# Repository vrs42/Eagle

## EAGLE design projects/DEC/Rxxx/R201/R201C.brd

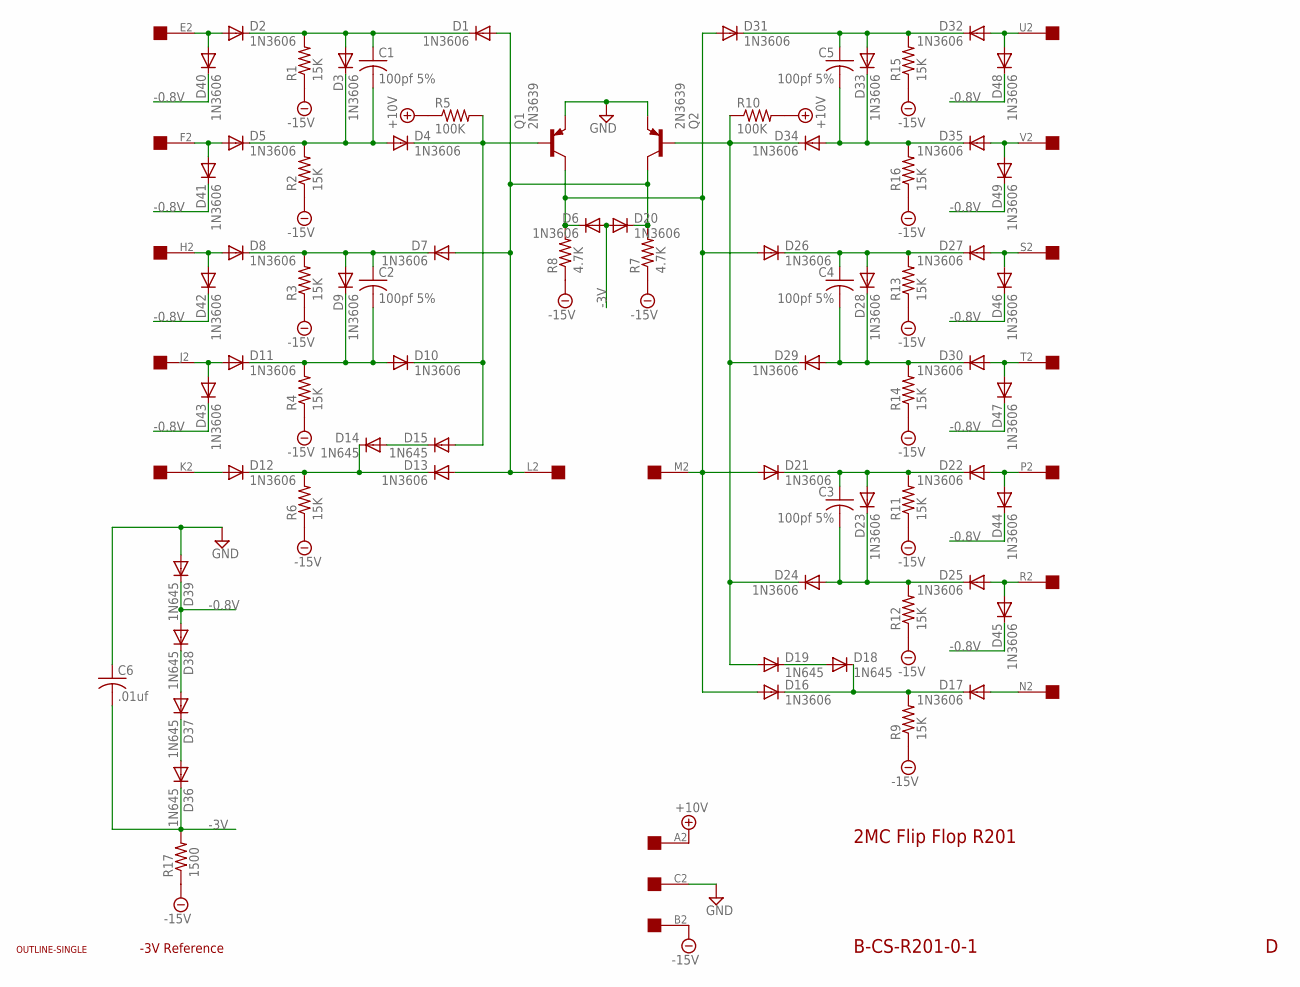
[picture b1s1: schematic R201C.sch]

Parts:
C1, C2, C3, C4, C5: 100pf 5%; C050-025X075
C6: .01uf; C050-025X075
D1, D2, D3, D4, D5, D6, D7, D8, D9, D10, D11, D12, D13, D16, D17, D20, D21, D22, D23, D24, D25, D26, D27, D28, D29, D30, D31, D32, D33, D34, D35, D40, D41, D42, D43, D44, D45, D46, D47, D48, D49: 1N3606; DO35-10
D14, D15, D18, D19, D36, D37, D38, D39: 1N645; DO35-10
Q1, Q2: 2N3639; TO39
R1, R2, R3, R4, R6, R9, R11, R12, R13, R14, R15, R16: 15K; 0207/10
R5, R10: 100K; 0207/10
R7, R8: 4.7K; 0207/10
R17: 1500; 0207/10
U$1: OUTLINE-SINGLE; SINGLE
U$2: EDGE-1; EDGE-CON1

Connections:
+10V: R5.1, R10.2, U$2.A2
-0.8V: D38.A, D39.C, D40.C, D41.C, D42.C, D43.C, D44.C, D45.C, D46.C, D47.C, D48.C, D49.C
-3V: C6.2, D6.A, D20.A, D36.C, R17.2
-15V: R1.1, R2.1, R3.1, R4.1, R6.1, R7.1, R8.1, R9.1, R11.1, R12.1, R13.1, R14.1, R15.1, R16.1, R17.1, U$2.B2
GND: C6.1, D39.A, Q1.1 (E), Q2.1 (E), U$2.C2
L: D1.A, D7.A, D13.A, D20.C, Q2.3 (C), R7.2, U$2.L2
M: D6.C, D16.A, D21.A, D26.A, D31.A, Q1.3 (C), R8.2, U$2.M2
unnamed: D5.A, D41.A, U$2.F2
unnamed: C5.1, D31.C, D32.C, D33.A, R15.2
unnamed: C1.2, D3.C, D4.A, D5.C, R2.2
unnamed: C1.1, D1.C, D2.C, D3.A, R1.2
unnamed: D12.A, U$2.K2
unnamed: D19.A, D24.C, D29.C, D34.C, Q2.2 (B), R10.1
unnamed: D32.A, D48.A, U$2.U2
unnamed: C5.2, D33.C, D34.A, D35.C, R16.2
unnamed: D17.A, U$2.N2
unnamed: D2.A, D40.A, U$2.E2
unnamed: D35.A, D49.A, U$2.V2
unnamed: D18.A, D19.C
unnamed: D37.A, D38.C
unnamed: D4.C, D10.C, D15.A, Q1.2 (B), R5.2
unnamed: D14.A, D15.C
unnamed: D36.A, D37.C
unnamed: D22.A, D44.A, U$2.P2
unnamed: D12.C, D13.C, D14.C, R6.2
unnamed: D8.A, D42.A, U$2.H2
unnamed: D16.C, D17.C, D18.C, R9.2
unnamed: D11.A, D43.A, U$2.J2
unnamed: C2.2, D9.C, D10.A, D11.C, R4.2
unnamed: D27.A, D46.A, U$2.S2
unnamed: C2.1, D7.C, D8.C, D9.A, R3.2
unnamed: D30.A, D47.A, U$2.T2
unnamed: C4.2, D28.C, D29.A, D30.C, R14.2
unnamed: C4.1, D26.C, D27.C, D28.A, R13.2
unnamed: D25.A, D45.A, U$2.R2
unnamed: C3.2, D23.C, D24.A, D25.C, R12.2
unnamed: C3.1, D21.C, D22.C, D23.A, R11.2

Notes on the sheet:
2MC Flip Flop R201
B-CS-R201-0-1
-3V Reference

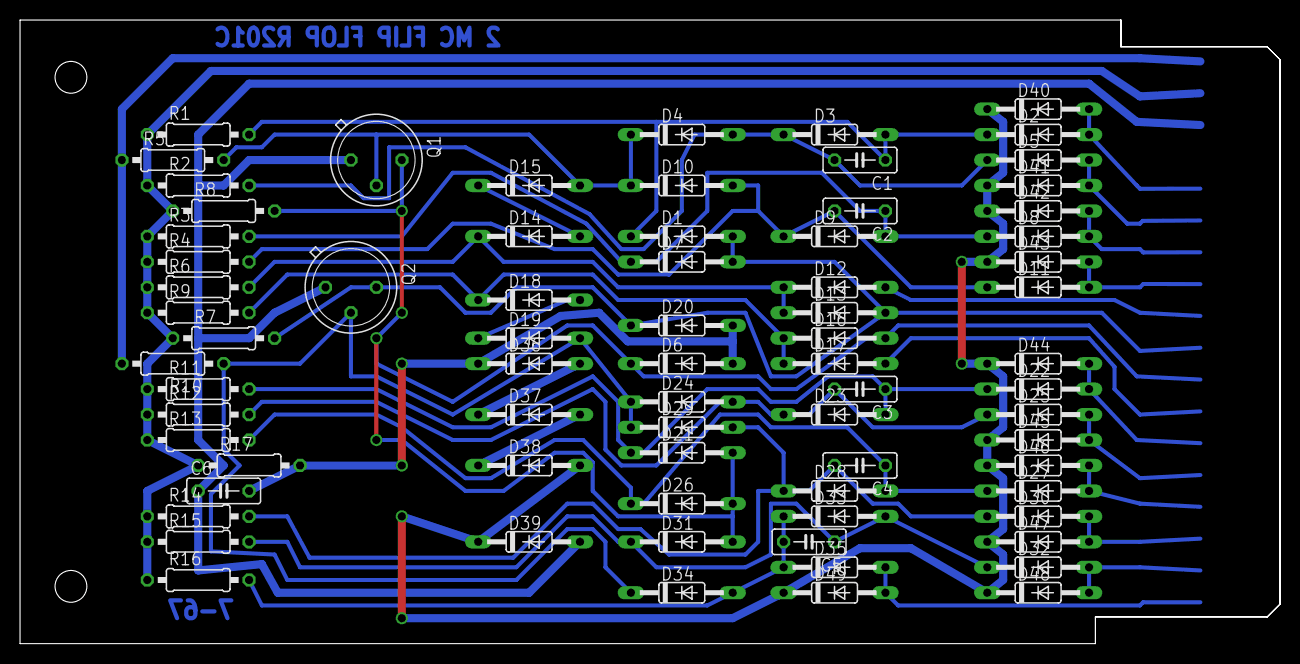
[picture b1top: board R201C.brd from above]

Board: 2 copper layers, 125.7 x 62.2 mm, 76 parts (0 on the bottom side), 37 nets.

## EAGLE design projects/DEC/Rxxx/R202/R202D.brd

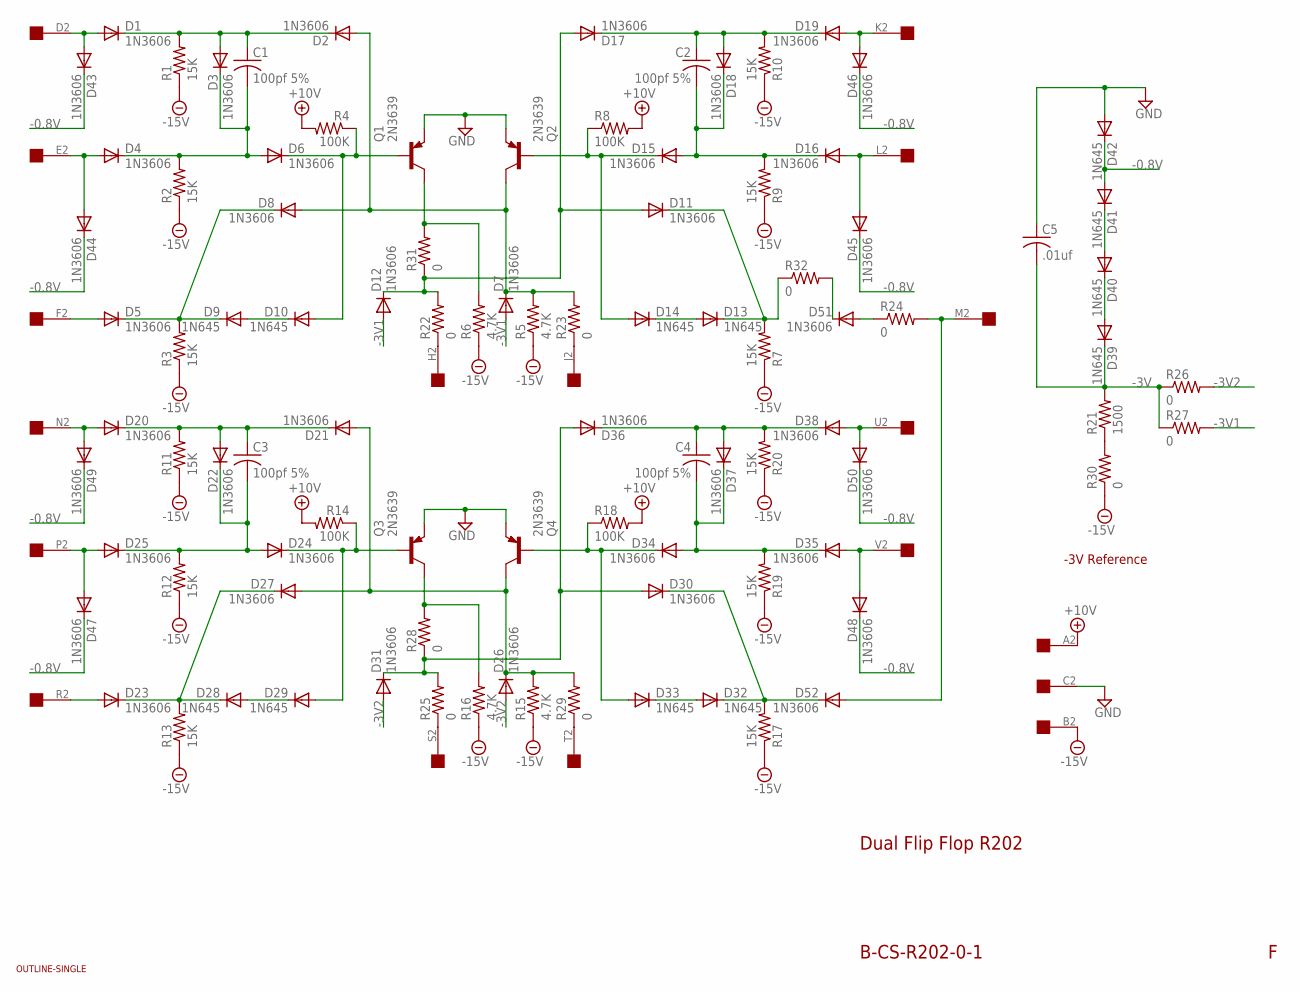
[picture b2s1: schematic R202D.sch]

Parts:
C1, C2, C3, C4: 100pf 5%; C050-025X075
C5: .01uf; C050-025X075
D1, D2, D3, D4, D5, D6, D7, D8, D11, D12, D15, D16, D17, D18, D19, D20, D21, D22, D23, D24, D25, D26, D27, D30, D31, D34, D35, D36, D37, D38, D43, D44, D45, D46, D47, D48, D49, D50, D51, D52: 1N3606; DO35-10
D9, D10, D13, D14, D28, D29, D32, D33, D39, D40, D41, D42: 1N645; DO35-10
Q1, Q2, Q3, Q4: 2N3639; TO39
R1, R2, R3, R7, R9, R10, R11, R12, R13, R17, R19, R20: 15K; 0207/10
R4, R8, R14, R18: 100K; 0207/10
R5, R6, R15, R16: 4.7K; 0207/10
R21: 1500; 0207/10
R22, R23, R24, R25, R26, R27, R28, R29, R30, R31, R32: 0; 0207/10
U$1: OUTLINE-SINGLE; SINGLE
U$2: EDGE-1; EDGE-CON1

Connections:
+10V: R4.2, R8.2, R14.2, R18.2, U$2.A2
-0.8V: D41.A, D42.C, D43.C, D44.C, D45.C, D46.C, D47.C, D48.C, D49.C, D50.C
-3V: C5.2, D39.C, R21.2, R26.1, R27.1
-3V1: D7.A, D12.A, R27.2
-3V2: D26.A, D31.A, R26.2
-15V: R1.1, R2.1, R3.1, R5.1, R6.1, R7.1, R9.1, R10.1, R11.1, R12.1, R13.1, R15.1, R16.1, R17.1, R19.1, R20.1, R30.1, U$2.B2
GND: C5.1, D42.A, Q1.1 (E), Q2.1 (E), Q3.1 (E), Q4.1 (E), U$2.C2
H: D11.A, D12.C, D17.A, R22.2, R31.1
J: D2.A, D7.C, D8.A, Q2.3 (C), R5.2, R23.2
unnamed: Q3.3 (C), R16.2, R28.2
unnamed: C2.1, D17.C, D18.A, D19.C, R10.2
unnamed: C1.2, D3.C, D4.C, D6.A, R2.2
unnamed: D1.A, D43.A, U$2.D2
unnamed: D4.A, D44.A, U$2.E2
unnamed: D13.A, D14.C
unnamed: D19.A, D46.A, U$2.K2
unnamed: C2.2, D15.A, D16.C, D18.C, R9.2
unnamed: D5.C, D8.C, D9.C, R3.2
unnamed: D5.A, U$2.F2
unnamed: D16.A, D45.A, U$2.L2
unnamed: D11.C, D13.C, R7.2, R32.1
unnamed: D40.A, D41.C
unnamed: D6.C, D10.A, Q1.2 (B), R4.1
unnamed: D52.A, R24.2, U$2.M2
unnamed: D39.A, D40.C
unnamed: D14.A, D15.C, Q2.2 (B), R8.1
unnamed: C3.1, D20.C, D21.C, D22.A, R11.2
unnamed: D28.A, D29.C
unnamed: D20.A, D49.A, U$2.N2
unnamed: C3.2, D22.C, D24.A, D25.C, R12.2
unnamed: C1.1, D1.C, D2.C, D3.A, R1.2
unnamed: D9.A, D10.C
unnamed: D25.A, D47.A, U$2.P2
unnamed: D23.C, D27.C, D28.C, R13.2
unnamed: D23.A, U$2.R2
unnamed: D24.C, D29.A, Q3.2 (B), R14.1
unnamed: C4.1, D36.C, D37.A, D38.C, R20.2
unnamed: D32.A, D33.C
unnamed: D38.A, D50.A, U$2.U2
unnamed: C4.2, D34.A, D35.C, D37.C, R19.2
unnamed: D35.A, D48.A, U$2.V2
unnamed: R22.1, U$2.H2
unnamed: D33.A, D34.C, Q4.2 (B), R18.1
unnamed: D30.C, D32.C, D52.C, R17.2
unnamed: R23.1, U$2.J2
unnamed: D51.A, R24.1
unnamed: R25.1, U$2.S2
unnamed: R29.1, U$2.T2
unnamed: R21.1, R30.2
unnamed: Q1.3 (C), R6.2, R31.2
unnamed: D51.C, R32.2
S: D30.A, D31.C, D36.A, R25.2, R28.1
T: D21.A, D26.C, D27.A, Q4.3 (C), R15.2, R29.2

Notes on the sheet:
Dual Flip Flop R202
B-CS-R202-0-1
-3V Reference

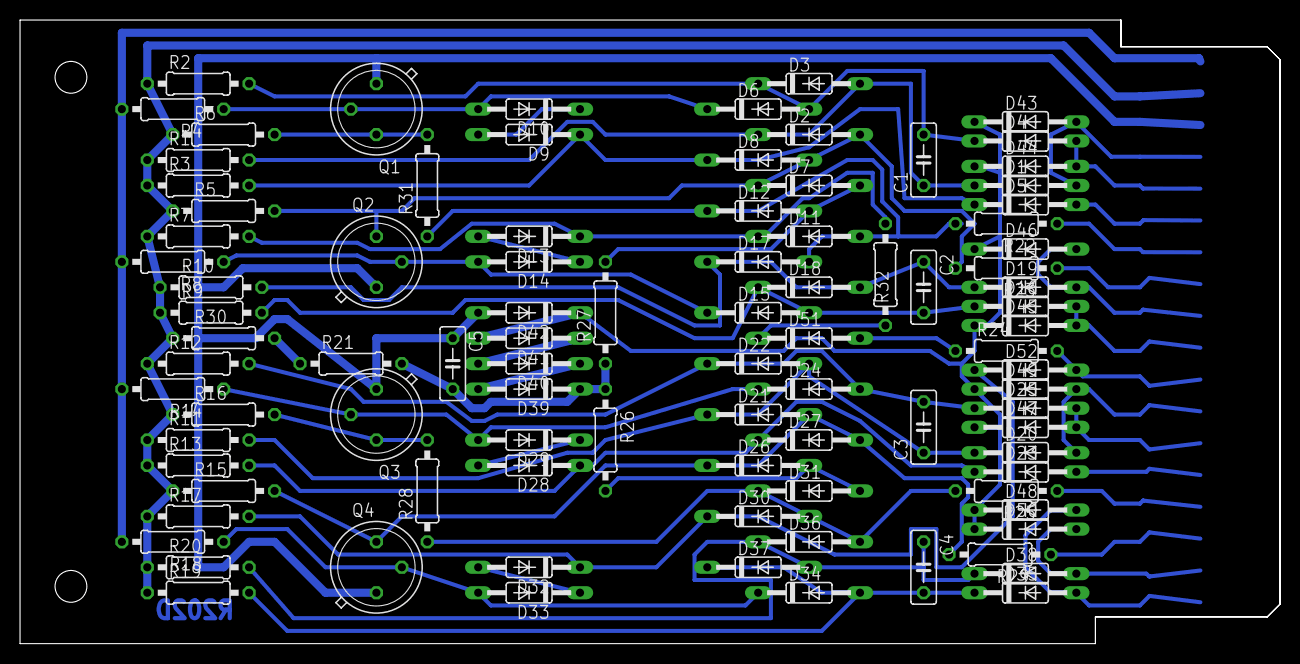
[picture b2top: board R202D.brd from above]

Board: 2 copper layers, 125.7 x 62.2 mm, 95 parts (0 on the bottom side), 53 nets.

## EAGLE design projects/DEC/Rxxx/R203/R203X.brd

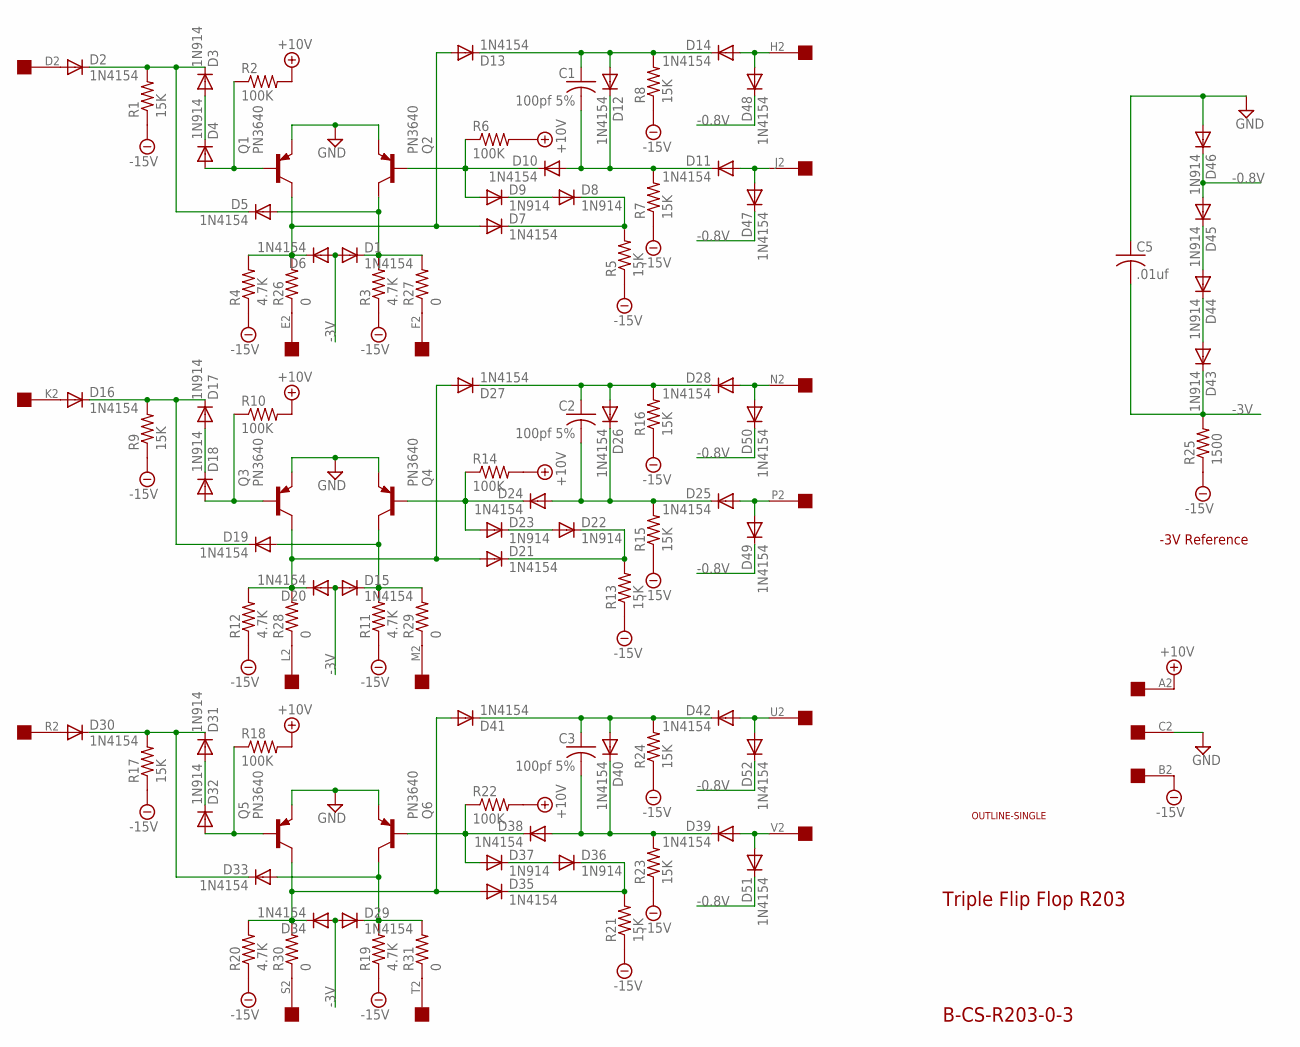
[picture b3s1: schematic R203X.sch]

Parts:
C1, C2, C3: 100pf 5%; C050-025X075
C5: .01uf; C050-025X075
D1, D2, D5, D6, D7, D10, D11, D12, D13, D14, D15, D16, D19, D20, D21, D24, D25, D26, D27, D28, D29, D30, D33, D34, D35, D38, D39, D40, D41, D42, D47, D48, D49, D50, D51, D52: 1N4154; DO35-10
D3, D4, D8, D9, D17, D18, D22, D23, D31, D32, D36, D37, D43, D44, D45, D46: 1N914; DO35-10
Q1, Q2, Q3, Q4, Q5, Q6: PN3640; TO39
R1, R5, R7, R8, R9, R13, R15, R16, R17, R21, R23, R24: 15K; 0207/10
R2, R6, R10, R14, R18, R22: 100K; 0207/10
R3, R4, R11, R12, R19, R20: 4.7K; 0207/10
R25: 1500; 0207/10
R26, R27, R28, R29, R30, R31: 0; 0207/10
U$1: OUTLINE-SINGLE; SINGLE
U$2: EDGE-1; EDGE-CON1

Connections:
+10V: R2.2, R6.2, R10.2, R14.2, R18.2, R22.2, U$2.A2
-0.8V: D45.A, D46.C, D47.C, D48.C, D49.C, D50.C, D51.C, D52.C
-3V: C5.2, D1.A, D6.A, D15.A, D20.A, D29.A, D34.A, D43.C, R25.2
-15V: R1.1, R3.1, R4.1, R5.1, R7.1, R8.1, R9.1, R11.1, R12.1, R13.1, R15.1, R16.1, R17.1, R19.1, R20.1, R21.1, R23.1, R24.1, R25.1, U$2.B2
E: D6.C, D7.A, D13.A, Q1.3 (C), R4.2, R26.2
F: D1.C, D5.A, Q2.3 (C), R3.2, R27.2
GND: C5.1, D46.A, Q1.1 (E), Q2.1 (E), Q3.1 (E), Q4.1 (E), Q5.1 (E), Q6.1 (E), U$2.C2
L: D20.C, D21.A, D27.A, Q3.3 (C), R12.2, R28.2
M: D15.C, D19.A, Q4.3 (C), R11.2, R29.2
unnamed: D31.A, D32.C
unnamed: C1.1, D12.A, D13.C, D14.C, R8.2
unnamed: D30.C, D31.C, D33.C, R17.2
unnamed: D30.A, U$2.R2
unnamed: D8.A, D9.C
unnamed: D14.A, D48.A, U$2.H2
unnamed: C1.2, D10.A, D11.C, D12.C, R7.2
unnamed: D2.C, D3.C, D5.C, R1.2
unnamed: D2.A, U$2.D2
unnamed: D11.A, D47.A, U$2.J2
unnamed: D7.C, D8.C, R5.2
unnamed: D44.A, D45.C
unnamed: D4.A, Q1.2 (B), R2.1
unnamed: D32.A, Q5.2 (B), R18.1
unnamed: D43.A, D44.C
unnamed: D9.A, D10.C, Q2.2 (B), R6.1
unnamed: C3.1, D40.A, D41.C, D42.C, R24.2
unnamed: D17.A, D18.C
unnamed: D36.A, D37.C
unnamed: D42.A, D52.A, U$2.U2
unnamed: C3.2, D38.A, D39.C, D40.C, R23.2
unnamed: D3.A, D4.C
unnamed: D39.A, D51.A, U$2.V2
unnamed: D16.C, D17.C, D19.C, R9.2
unnamed: D16.A, U$2.K2
unnamed: D18.A, Q3.2 (B), R10.1
unnamed: C2.1, D26.A, D27.C, D28.C, R16.2
unnamed: D22.A, D23.C
unnamed: D28.A, D50.A, U$2.N2
unnamed: C2.2, D24.A, D25.C, D26.C, R15.2
unnamed: D25.A, D49.A, U$2.P2
unnamed: R26.1, U$2.E2
unnamed: D23.A, D24.C, Q4.2 (B), R14.1
unnamed: D21.C, D22.C, R13.2
unnamed: R27.1, U$2.F2
unnamed: D37.A, D38.C, Q6.2 (B), R22.1
unnamed: R28.1, U$2.L2
unnamed: R29.1, U$2.M2
unnamed: D35.C, D36.C, R21.2
unnamed: R30.1, U$2.S2
unnamed: R31.1, U$2.T2
S: D34.C, D35.A, D41.A, Q5.3 (C), R20.2, R30.2
T: D29.C, D33.A, Q6.3 (C), R19.2, R31.2

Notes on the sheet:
Triple Flip Flop R203
B-CS-R203-0-3
-3V Reference

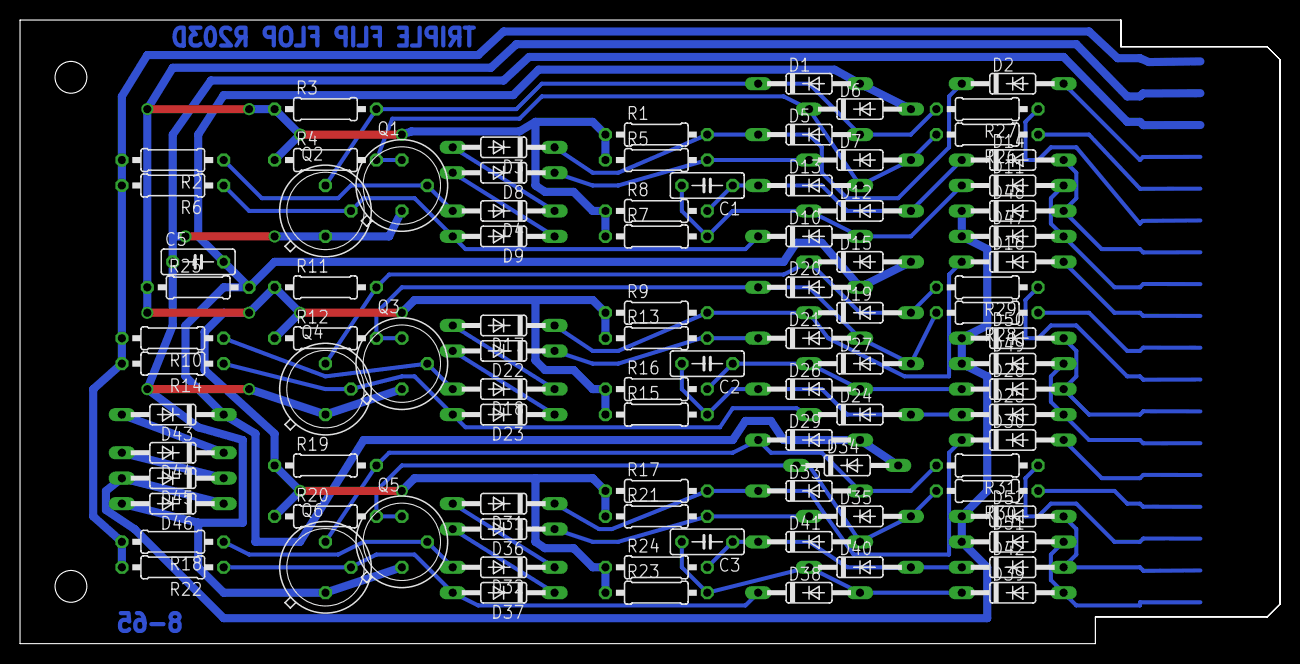
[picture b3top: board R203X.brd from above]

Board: 2 copper layers, 125.7 x 62.2 mm, 95 parts (0 on the bottom side), 52 nets.
